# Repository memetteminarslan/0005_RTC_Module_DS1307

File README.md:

# 0005_RTC_Module_DS1307

You are seeing a large number of widely used RTC modules in electronic development kits. More information coming soon...

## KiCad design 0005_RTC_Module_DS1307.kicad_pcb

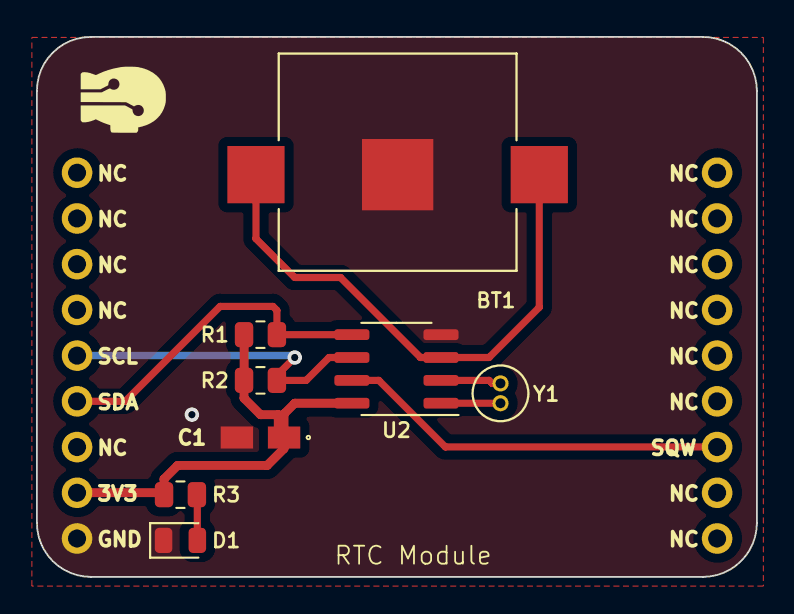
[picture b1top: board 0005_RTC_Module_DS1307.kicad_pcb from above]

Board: 2 copper layers, 40.0 x 30.0 mm, 9 parts (0 on the bottom side), 9 nets.

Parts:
BT1: 3000TR; BAT_3000TR
C1: 0.1uF; T491A
D1: LED; LED_0805_2012Metric
R1, R2: 2.2k; R_0805_2012Metric
R3: 470r; R_0805_2012Metric
U1: pin_header
U2: DS1307Z+; SOIC-8_3.9x4.9mm_P1.27mm
Y1: 32.768Khz; XTAL_ECS-.327-12.5-8X-C

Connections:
+3V3: C1.1, R1.1, R2.1, R3.1, U1.8 (3V3), U2.8 (VCC)
GND: BT1.N, C1.2, D1.1 (K), U1.9 (GND), U2.4 (GND)
unnamed: D1.2 (A), R3.2
unnamed: BT1.P1, BT1.P2, U2.3 (VBAT)
unnamed: U2.1 (X1), Y1.2
unnamed: U2.2 (X2), Y1.1
SCL: R2.2, U1.5 (SCL), U2.6 (SCL)
SDA: R1.2, U1.6 (SDA), U2.5 (SDA)
SQW: U1.12 (GPIO), U2.7 (SQW/OUT)
